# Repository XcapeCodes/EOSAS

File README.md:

# EOSAS - Embedded Optical Skin Analysis System

EOSAS is an embedded imaging prototype developed to explore hardware/software integration, computer vision, and machine learning.

The system combines an ESP32-CAM for image acquisition, a Particle Argon for physical controls and system status, a custom dual-MCU PCB, C/C++ firmware, and a Python-based Flask/OpenCV/TensorFlow processing pipeline.

> **Note:** EOSAS is an educational engineering prototype. It is not a medical device and is not intended for diagnosis, treatment, or clinical use.

## Overview

EOSAS captures skin images using an ESP32-CAM, processes them through a machine learning pipeline, and displays results through a custom Flask dashboard. A Particle Argon controls the user interface, including scan lighting, button controls, and hazard indication LEDs.

*Figure 1. High-level EOSAS system architecture showing embedded hardware, communication, machine learning pipeline, and dashboard outputs.*

## 🎥 Demo Video

A demonstration of the current EOSAS prototype can be found in the `demo` folder:

➡️ **eosas_demo.mov**

If GitHub does not preview the video directly, download the file to view the full demonstration.

## Project Status

### Completed
- Breadboard-based functional prototype
- ESP32-CAM image acquisition
- Particle Argon control firmware
- Flask dashboard and inference pipeline
- Custom PCB schematic and layout
- ERC/DRC verification

### In Progress
- PCB fabrication and bring-up
- Hardware validation
- Optical sensor calibration
- Custom enclosure

### Planned
- PCB revision based on bring-up results
- Battery-powered operation
- Improved wireless reliability
- Additional model/data evaluation

## Custom PCB

EOSAS PCB v1.0 is a custom dual-MCU carrier board designed to replace the breadboard wiring used in the original prototype and consolidate the system electronics onto a dedicated PCB.

The board integrates:
- Particle Argon and ESP32-CAM
- USB-C power input and protection
- Optical sensing
- Controlled scan illumination
- Low / Medium / High hazard indicators
- Power and scan controls
- Programming, expansion, and debugging interfaces

**Status:** Design complete; fabrication and physical validation pending.

Full PCB design files, schematic, layout, and documentation are available in the [`PCB/`](PCB/) directory.

## Features

* ESP32-CAM image capture
* Machine learning image classification
* Flask-based AI server
* Real-time dashboard visualization
* Particle Argon hardware controller
* White illumination LEDs
* Hazard indication LEDs (Green / Yellow / Red)
* Wi-Fi setup portal
* SD card image logging
* Portable multi-network deployment

## Hardware

- ESP32-CAM with OV2640 camera
- Particle Argon
- EOSAS PCB v1.0
- TEMT6000 optical light sensor
- White scan illumination
- Low / Medium / High hazard LEDs
- Scan push button
- Power switch
- USB-C 5 V power input
- External illumination connector
- ESP32 programming header
- Expansion/debug header
- SD card storage
  
## Software

* Python
* Flask
* TensorFlow / Keras
* OpenCV
* C++
* Arduino Framework
* Particle Device OS

## System Workflow

1. User powers on EOSAS
2. Particle Argon initializes the hardware
3. ESP32-CAM connects to the configured network
4. EOSAS locates the inference server
5. User positions the target skin area
6. User presses the Scan button
7. Optical sensor measures illumination conditions
8. White scan lighting is activated
9. ESP32-CAM captures the image
10. Image is sent to the Python inference server
11. OpenCV preprocesses the image
12. TensorFlow generates the hazard prediction
13. Hazard score and confidence are calculated
14. Results are displayed on the dashboard
15. EOSAS updates the Low / Medium / High hazard indicator LED

## Engineering Decisions & Tradeoffs

### Dual-MCU Architecture
The Particle Argon manages physical user controls, illumination, and status indicators, while the ESP32-CAM handles image acquisition and network communication. This separates hardware-control responsibilities from camera and image-transfer tasks.

### Custom PCB
PCB v1.0 consolidates the original breadboard wiring into a dedicated carrier board with USB-C power/protection, optical sensing, illumination control, status indicators, and programming/debug interfaces.

### Controlled Illumination
White scan LEDs and an optical light sensor are included to support more consistent image-capture conditions and future calibration work.

### Debug and Expansion Access
Programming and debug interfaces were included to simplify board bring-up, firmware development, and future hardware revisions.

## Future Improvements

- Fabricate and validate EOSAS PCB v1.0
- Complete optical sensor calibration
- Build PCB-based custom enclosure
- Add battery-powered operation
- Improve hazard scoring
- Expand training data with EOSAS-captured images
- Improve condition-matching model
- Add automatic server discovery
- Improve wireless communication reliability

## Repository Structure

```text
EOSAS/
├── Firmware/   Embedded firmware and device control
├── PCB/        KiCad schematic, layout, renders, and documentation
├── Software/   Flask/OpenCV/TensorFlow application code
├── models/     Machine-learning models and related files
├── demo/       Prototype demonstration
└── images/     Architecture diagrams and project media
```

## Third-Party

Portions of the ESP32 camera-server implementation are based on Espressif reference/example code and remain subject to their respective licensing terms.

EOSAS-specific hardware design, system integration, control firmware, software, and modifications are documented separately within this repository.

## Author

Mishael Agbali

Electrical Engineering Student
University of South Florida

LinkedIn:
https://www.linkedin.com/in/mishael-agbali/

GitHub:
https://github.com/XcapeCodes

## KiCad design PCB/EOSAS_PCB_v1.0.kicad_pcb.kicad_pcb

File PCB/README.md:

[← Back to main EOSAS documentation](../README.md)
# EOSAS PCB v1.0

EOSAS PCB v1.0 is a custom dual-MCU carrier board designed to replace the breadboard wiring used in the original EOSAS prototype and consolidate the system electronics onto a dedicated PCB.

## Current Status

**Design complete — fabrication and physical validation pending.**

- Schematic completed
- PCB routing completed
- ERC passed
- DRC passed
- Ground plane completed
- Silkscreen and module outlines added
- 3D board layout reviewed

## PCB Features

- Particle Argon and ESP32-CAM integration
- USB-C 5 V power input
- Input fuse and power control
- Power status indicator
- TEMT6000 optical sensor interface
- MOSFET-controlled white scan illumination
- Low / Medium / High hazard indicator LEDs
- Separate power and scan controls
- ESP32 programming header
- Expansion interface
- External illumination connector
- Debug test points
- ESP32-CAM bulk capacitance for power stability
- Four mounting points for enclosure integration

## Design

### Schematic

### PCB Layout

### 3D Render

## Architecture

The Particle Argon serves as the primary hardware controller, managing user inputs, illumination, optical sensing, and hazard indicators. The ESP32-CAM handles image acquisition and communication with the EOSAS inference server.

The two controllers communicate through the PCB's dedicated interface, allowing the embedded hardware and image-processing pipeline to operate as one system.

## Next Steps

- Complete final pre-fabrication review
- Generate manufacturing files
- Fabricate PCB v1.0
- Assemble and perform board bring-up
- Validate power rails and interfaces
- Test Argon-to-ESP32 communication
- Calibrate optical sensing and scan illumination
- Integrate PCB into the final EOSAS enclosure
- Complete full system validation

> EOSAS is an experimental engineering project and is not intended to provide medical diagnoses.

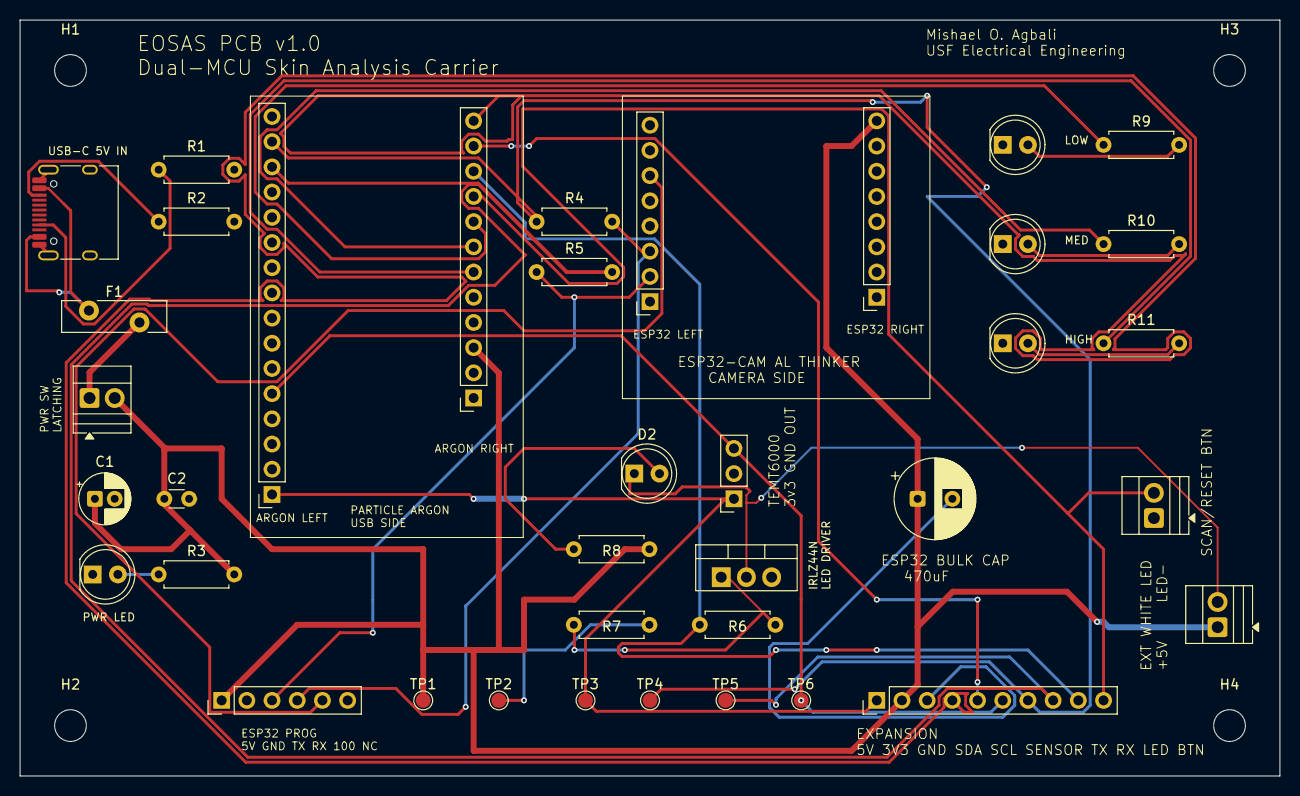
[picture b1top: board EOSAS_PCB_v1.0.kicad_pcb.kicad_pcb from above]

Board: 2 copper layers, 127.0 x 76.2 mm, 42 parts (0 on the bottom side), 27 nets.

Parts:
C1: 10uF; CP_Radial_D5.0mm_P2.00mm
C2: 0.1uF; C_Disc_D3.0mm_W1.6mm_P2.50mm
C3: 470uF_ESP32_BULK; CP_Radial_D8.0mm_P3.50mm
D1: PWR_LED; LED_D5.0mm
D2: SCAN_WHITE_LED; LED_D5.0mm
D3: LOW_HAZARD_LED; LED_D5.0mm
D4: MED_HAZARD_LED; LED_D5.0mm
D5: HIGH_HAZARD_LED; LED_D5.0mm
F1: 1.5A_POLYFUSE; Fuse_Bourns_MF-RG500
H1, H2, H3, H4: MountingHole; MountingHole_3.2mm_M3
J1: USB_C_5V_IN; USB_C_Receptacle_HRO_TYPE-C-31-M-12
J2: EXT_WHITE_LED; TerminalBlock_Xinya_XY308-2.54-2P_1x02_P2.54mm_Horizontal
J2ARGON_LEFT1: ARGON_LEFT_SOCKET; PinSocket_1x16_P2.54mm_Vertical
J2ESP32_RIGHT1: ESP32_CAM_RIGHT_SOCKET; PinSocket_1x08_P2.54mm_Vertical
J3ARGON_RIGHT1: ARGON_RIGHT_SOCKET; PinSocket_1x12_P2.54mm_Vertical
J3ESP32_LEFT1: ESP32_CAM_LEFT_SOCKET; PinSocket_1x08_P2.54mm_Vertical
J6ESP32_PROG1: ESP32_PROG_HEADER; PinHeader_1x06_P2.54mm_Vertical
J7TEMT6000: TEMT6000_SENSOR; PinSocket_1x03_P2.54mm_Vertical
J8EXPANSION1: EXPANSION_HEADER; PinHeader_1x10_P2.54mm_Vertical
Q2: IRLZ44N_LED_DRIVER; TO-220-3_Vertical
R1, R2: 5.1K; R_Axial_DIN0207_L6.3mm_D2.5mm_P7.62mm_Horizontal
R3, R4, R5: 1K; R_Axial_DIN0207_L6.3mm_D2.5mm_P7.62mm_Horizontal
R6, R8: 220; R_Axial_DIN0207_L6.3mm_D2.5mm_P7.62mm_Horizontal
R7: 100K; R_Axial_DIN0207_L6.3mm_D2.5mm_P7.62mm_Horizontal
R9, R10, R11: 1k; R_Axial_DIN0207_L6.3mm_D2.5mm_P7.62mm_Horizontal
SW1: EXT_PWR_SW; TerminalBlock_Xinya_XY308-2.54-2P_1x02_P2.54mm_Horizontal
SW2_BUTTON1: SCAN_RESET_BTN; TerminalBlock_Xinya_XY308-2.54-2P_1x02_P2.54mm_Horizontal
TP1: 5V; TestPoint_Pad_D1.5mm
TP2: GND; TestPoint_Pad_D1.5mm
TP3: 3V3; TestPoint_Pad_D1.5mm
TP4: ARGON_TX; TestPoint_Pad_D1.5mm
TP5: ARGON_RX; TestPoint_Pad_D1.5mm
TP6: SENSOR_OUT; TestPoint_Pad_D1.5mm

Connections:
+3V3: J2ARGON_LEFT1.1, J7TEMT6000.1, J8EXPANSION1.1, TP3.1 (1_1)
+5V: C1.1, C2.1, C3.1, J2.1, J3ARGON_RIGHT1.3, J3ESP32_LEFT1.8, J6ESP32_PROG1.1, J8EXPANSION1.2, R3.2, R8.2, SW1.2 (B), TP1.1 (1_1)
/ARGON_RX: J2ARGON_LEFT1.14, J8EXPANSION1.8, R5.2, TP5.1 (1_1)
/ARGON_TX: J2ARGON_LEFT1.15, J8EXPANSION1.7, R4.1, TP4.1 (1_1)
/BUTTON_IN: J3ARGON_RIGHT1.9, J8EXPANSION1.10, SW2_BUTTON1.2
/ESP32_IO0: J2ESP32_RIGHT1.6, J6ESP32_PROG1.5
/ESP32_RX: J2ESP32_RIGHT1.3, J6ESP32_PROG1.4, R4.2
/ESP32_TX: J2ESP32_RIGHT1.2, J6ESP32_PROG1.3, R5.1
/EXP_SCL: J3ARGON_RIGHT1.11, J8EXPANSION1.5
/EXP_SDA: J3ARGON_RIGHT1.12, J8EXPANSION1.4
/GREEN_LED_CTRL: J3ARGON_RIGHT1.8, R9.1
/LED_NEG: D2.1 (K), J2.2, Q2.2 (D)
/RED_LED_CTRL: J3ARGON_RIGHT1.6, R11.1
/SENSOR_OUT: J2ARGON_LEFT1.5, J7TEMT6000.3, J8EXPANSION1.6, TP6.1 (1_1)
/WHITE_LED_CTRL: J3ARGON_RIGHT1.10, J8EXPANSION1.9, R6.1
/YELLOW_LED_CTRL: J3ARGON_RIGHT1.7, R10.1
GND: C1.2, C2.2, C3.2, D1.1 (K), D3.1 (K), D4.1 (K), D5.1 (K), J1.A1 (GND), J1.A12 (GND), J1.B1 (GND), J1.B12 (GND), J1.SH (SHIELD), J2ARGON_LEFT1.4, J2ESP32_RIGHT1.1, J2ESP32_RIGHT1.5, J3ESP32_LEFT1.7, J6ESP32_PROG1.2, J7TEMT6000.2, J8EXPANSION1.3, Q2.3 (S), R1.2, R2.2, R7.2, SW2_BUTTON1.1, TP2.1 (1_1)
unnamed: D1.2 (A), R3.1
unnamed: D2.2 (A), R8.1
unnamed: D3.2 (A), R9.2
unnamed: D4.2 (A), R10.2
unnamed: D5.2 (A), R11.2
unnamed: F1.1, J1.A4 (VBUS), J1.A9 (VBUS), J1.B4 (VBUS), J1.B9 (VBUS)
unnamed: J1.A5 (CC1), R1.1
unnamed: J1.B5 (CC2), R2.1
unnamed: Q2.1 (G), R6.2, R7.1
unnamed: F1.2, SW1.1 (A)

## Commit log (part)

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2026-06-03 Create Firmware
2026-06-03 Create Software
2026-06-03 Create Demo
2026-06-04 Initial EOSAS project upload
2026-06-04 update 2
